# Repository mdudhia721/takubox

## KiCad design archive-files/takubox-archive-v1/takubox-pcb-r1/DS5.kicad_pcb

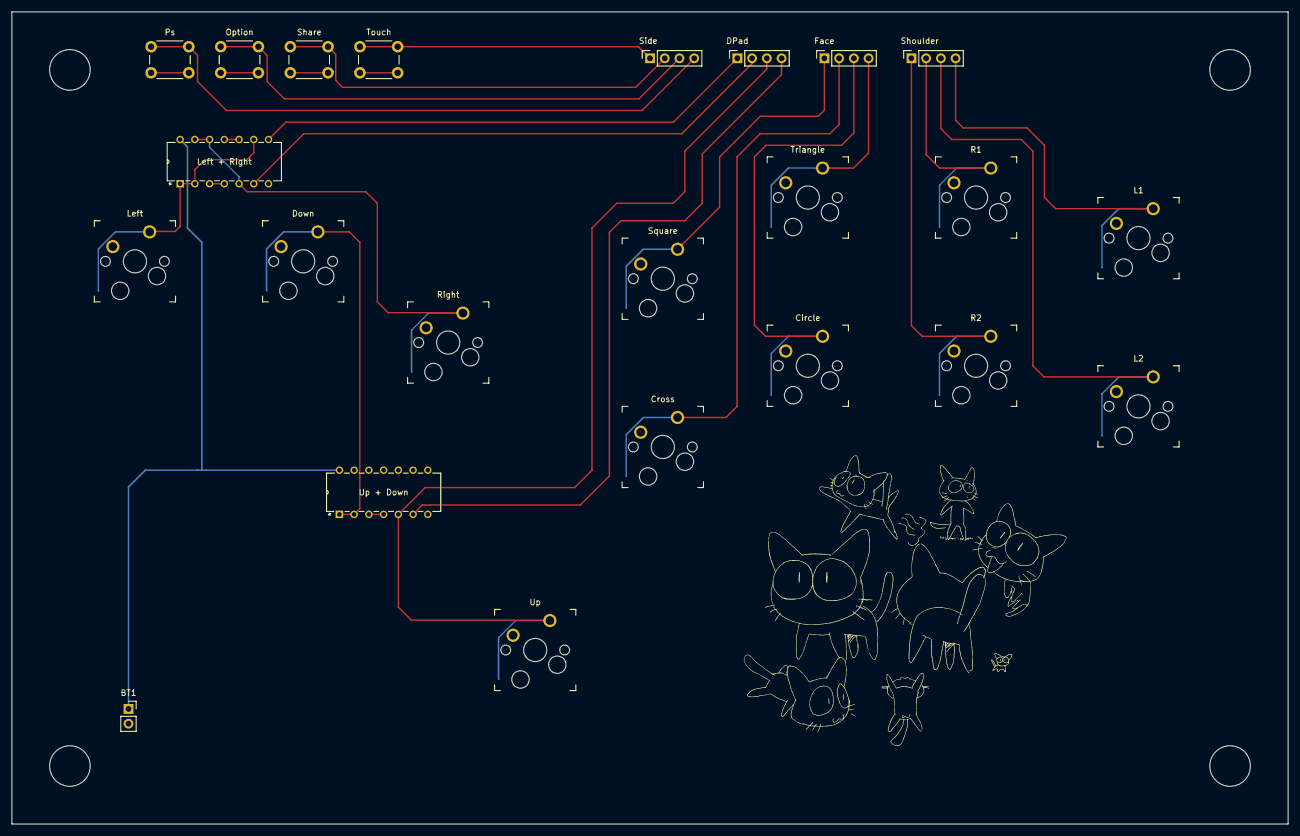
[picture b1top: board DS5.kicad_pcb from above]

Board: 2 copper layers, 220.0 x 140.0 mm, 23 parts (0 on the bottom side), 24 nets.

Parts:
BT1: Battery; PinSocket_1x02_P2.54mm_Vertical
Circle: SW_DIP_x01; Kailh_socket_MX_optional
Cross: SW_DIP_x01; Kailh_socket_MX_optional
DPad1: Conn_01x04_Pin; PinSocket_1x04_P2.54mm_Vertical
Down: SW_DIP_x01; Kailh_socket_MX_optional
Face: Conn_01x04_Pin; PinSocket_1x04_P2.54mm_Vertical
L1, L2: SW_DIP_x01; Kailh_socket_MX_optional
Left: SW_DIP_x01; Kailh_socket_MX_optional
Left + Right: SN7400N; N14
Option: SW_DIP_x01; SW_PUSH_6mm
Ps: SW_DIP_x01; SW_PUSH_6mm
R1, R2: SW_DIP_x01; Kailh_socket_MX_optional
Right: SW_DIP_x01; Kailh_socket_MX_optional
Share: SW_DIP_x01; SW_PUSH_6mm
Shoulder: Conn_01x04_Pin; PinSocket_1x04_P2.54mm_Vertical
Side: Conn_01x04_Pin; PinSocket_1x04_P2.54mm_Vertical
Square: SW_DIP_x01; Kailh_socket_MX_optional
Touch: SW_DIP_x01; SW_PUSH_6mm
Triangle: SW_DIP_x01; Kailh_socket_MX_optional
Up: SW_DIP_x01; Kailh_socket_MX_optional
Up + Down: SN7400N; N14

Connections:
/5V: BT1.1 (+), Left + Right.14 (VCC), Up + Down.14 (VCC)
/Down: DPad1.4, Up + Down.6 (2Y)
/L1: L1.1, Shoulder.4
/L2: L2.1, Shoulder.3
/Left: DPad1.2, Left + Right.6 (2Y)
/O: Circle.1, Face.3
/Option: Option.1, Side.3
/PS: Ps.1, Side.4
/R1: R1.1, Shoulder.2
/R2: R2.1, Shoulder.1
/Right: DPad1.1, Left + Right.8 (3Y)
/Share: Share.1, Side.2
/Touch: Side.1, Touch.1
/Up: DPad1.3, Up.1, Up + Down.5 (2B)
/X: Cross.1, Face.2
/□: Face.1, Square.1
/△: Face.4, Triangle.1
GND: BT1.2 (-), Circle.2, Cross.2, Down.2, L1.2, L2.2, Left.2, Left + Right.7 (GND), Option.2, Ps.2, R1.2, R2.2, Right.2, Share.2, Square.2, Touch.2, Triangle.2, Up.2, Up + Down.7 (GND)
unnamed: Left.1, Left + Right.1 (1A), Left + Right.2 (1B), Left + Right.9 (3A)
unnamed: Left + Right.3 (1Y), Left + Right.4 (2A)
unnamed: Left + Right.5 (2B), Left + Right.12 (4A), Left + Right.13 (4B), Right.1
unnamed: Left + Right.10 (3B), Left + Right.11 (4Y)
unnamed: Down.1, Up + Down.1 (1A), Up + Down.2 (1B)
unnamed: Up + Down.3 (1Y), Up + Down.4 (2A)

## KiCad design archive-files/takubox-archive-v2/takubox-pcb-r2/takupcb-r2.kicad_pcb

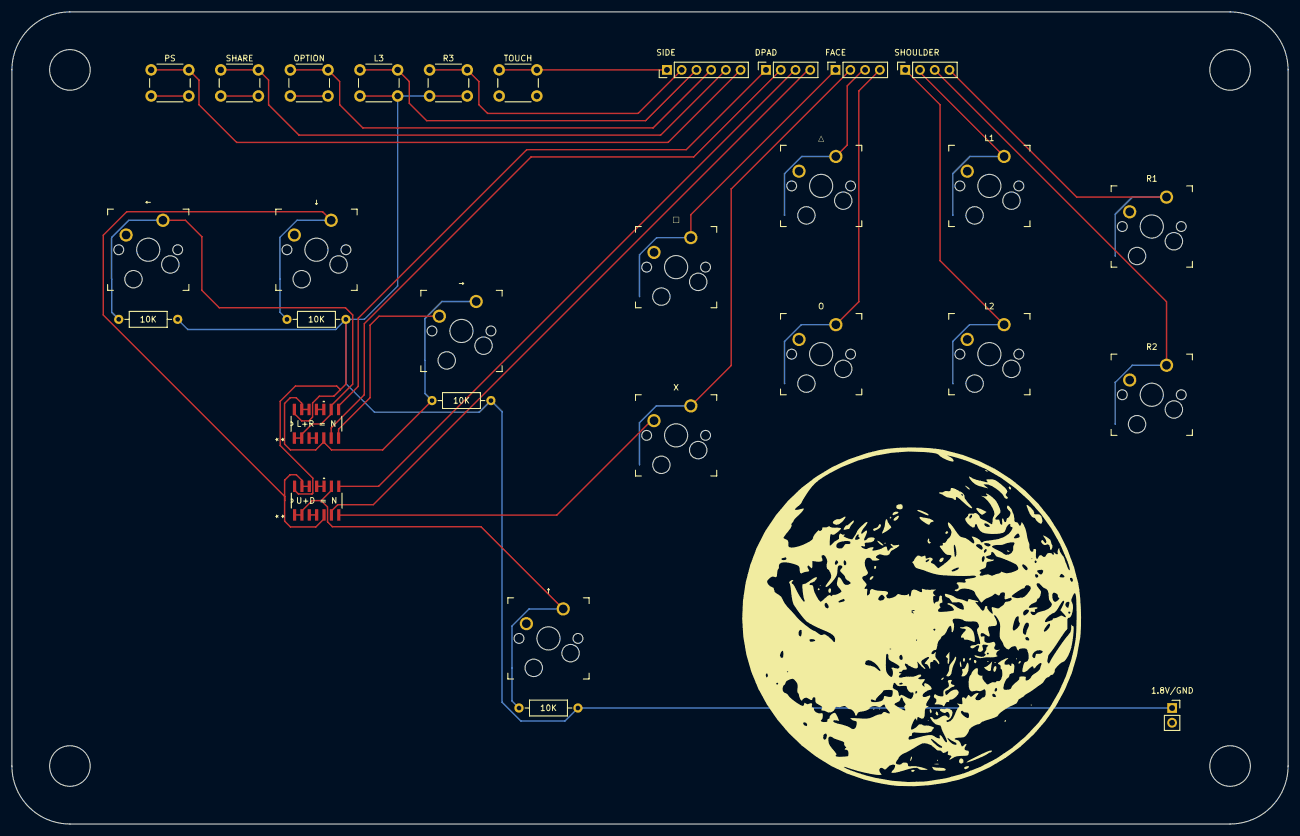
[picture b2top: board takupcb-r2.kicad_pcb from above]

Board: 2 copper layers, 220.0 x 140.0 mm, 29 parts (0 on the bottom side), 28 nets.

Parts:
1.8V/GND: Battery; PinSocket_1x02_P2.54mm_Vertical
10K, 10K#2, 10K#3, 10K#4: R; R_Axial_DIN0207_L6.3mm_D2.5mm_P10.16mm_Horizontal
DPAD: Conn_01x04_Pin; PinSocket_1x04_P2.54mm_Vertical
FACE: Conn_01x04_Pin; PinSocket_1x04_P2.54mm_Vertical
L1, L2: SW_DIP_x01; Kailh_socket_MX_optional
L3: SW_DIP_x01; SW_PUSH_6mm_H13mm
L+R = N: SN74LVC00ADR
O: SW_DIP_x01; Kailh_socket_MX_optional
OPTION: SW_DIP_x01; SW_PUSH_6mm_H13mm
PS: SW_DIP_x01; SW_PUSH_6mm_H13mm
R1, R2: SW_DIP_x01; Kailh_socket_MX_optional
R3: SW_DIP_x01; SW_PUSH_6mm_H13mm
SHARE: SW_DIP_x01; SW_PUSH_6mm_H13mm
SHOULDER: Conn_01x04_Pin; PinSocket_1x04_P2.54mm_Vertical
SIDE: Conn_01x06_Pin; PinHeader_1x06_P2.54mm_Vertical
TOUCH: SW_DIP_x01; SW_PUSH_6mm_H13mm
U+D = N: SN74LVC00ADR
X: SW_DIP_x01; Kailh_socket_MX_optional
←: SW_DIP_x01; Kailh_socket_MX_optional
↑: SW_DIP_x01; Kailh_socket_MX_optional
→: SW_DIP_x01; Kailh_socket_MX_optional
↓: SW_DIP_x01; Kailh_socket_MX_optional
□: SW_DIP_x01; Kailh_socket_MX_optional
△: SW_DIP_x01; Kailh_socket_MX_optional

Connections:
/1.8V: 1.8V/GND.1 (+), 10K.1, 10K#2.1, 10K#3.2, 10K#4.2, L3.2, L+R = N.14 (VCC), R3.2, U+D = N.14 (VCC)
/Down: DPAD.3, U+D = N.8 (3Y)
/L1: L1.1, SHOULDER.2
/L2: L2.1, SHOULDER.1
/L3: L3.1, SIDE.3
/Left: DPAD.2, L+R = N.6 (2Y)
/O: FACE.4, O.1
/Option: OPTION.1, SIDE.4
/PS: PS.1, SIDE.6
/R1: R1.1, SHOULDER.4
/R2: R2.1, SHOULDER.3
/R3: R3.1, SIDE.2
/Right: DPAD.1, L+R = N.8 (3Y)
/Share: SHARE.1, SIDE.5
/Touch: SIDE.1, TOUCH.1
/Up: DPAD.4, U+D = N.6 (2Y)
/X: FACE.2, X.1
/□: FACE.1, □.1
/△: FACE.3, △.1
GND: 1.8V/GND.2 (-), L1.2, L2.2, L+R = N.7 (GND), O.2, OPTION.2, PS.2, R1.2, R2.2, SHARE.2, TOUCH.2, U+D = N.7 (GND), X.2, ←.2, ↑.2, →.2, ↓.2, □.2, △.2
unnamed: 10K#2.2, L+R = N.1 (1A), L+R = N.2 (1B), L+R = N.9 (3A), ←.1
unnamed: L+R = N.3 (1Y), L+R = N.4 (2A)
unnamed: 10K#3.1, L+R = N.5 (2B), L+R = N.12 (4A), L+R = N.13 (4B), →.1
unnamed: L+R = N.10 (3B), L+R = N.11 (4Y)
unnamed: 10K.2, U+D = N.1 (1A), U+D = N.2 (1B), U+D = N.9 (3A), ↑.1
unnamed: U+D = N.3 (1Y), U+D = N.4 (2A)
unnamed: 10K#4.1, U+D = N.5 (2B), U+D = N.12 (4A), U+D = N.13 (4B), ↓.1
unnamed: U+D = N.10 (3B), U+D = N.11 (4Y)

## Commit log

2024-03-28 socd and display working, padhack
2024-03-28 init
2024-03-29 HID working
2024-04-06 Changed to MPG, working as of rn, need to do USB
2024-11-07 start over.
2024-11-19 new gamepad firmware started
2024-12-07 input update, display socd output next
2024-12-08 display donez
2024-12-08 socd
2024-12-08 Joystick HID
2024-12-08 reset interrupt
2024-12-08 output padhack
2025-01-23 some file renaming and inclusion of archive files
